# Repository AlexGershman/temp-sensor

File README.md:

# temp-sensor
This repo is dedicated to storing the schematic, layout, and symbol files of the temperature sensor circuit board for ECE 115D.

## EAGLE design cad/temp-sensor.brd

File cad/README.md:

In the CAD folder, we store files such as the BOM, schematic, board, and any new symbols.

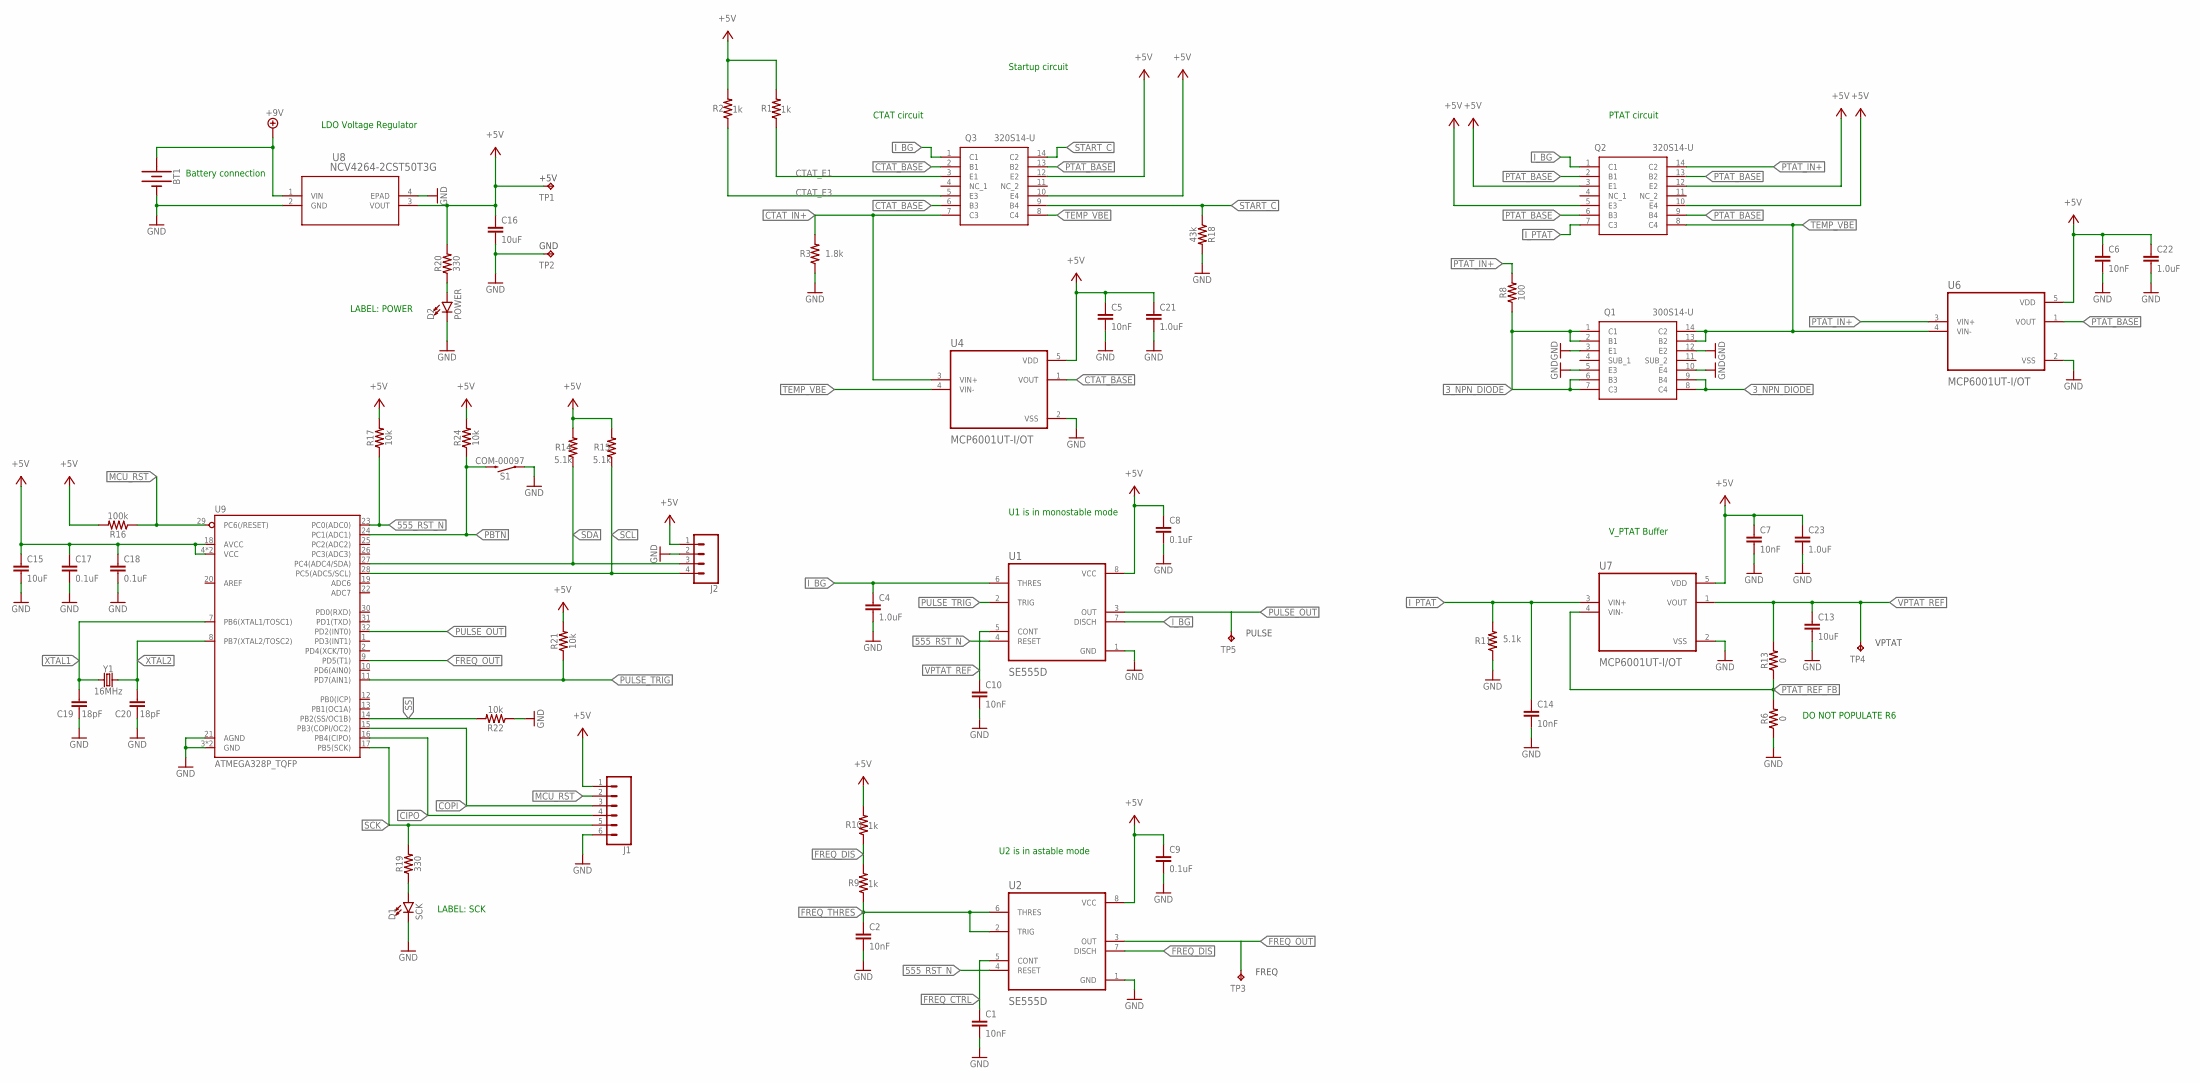
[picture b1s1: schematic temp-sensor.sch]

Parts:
BT1: BATTERY-9V; BATTCON_9V
C1, C2, C5, C6, C7, C10, C14: 10nF; 0603
C4, C21, C22, C23: 1.0uF; 0603
C8, C9, C17, C18: 0.1uF; 0603
C13, C15, C16: 10uF; 0805
C19, C20: 18pF; 0603
D1: SCK; LED-1206
D2: POWER; LED-1206
J1: CONN_06SILK_FEMALE_PTH; 1X06
J2: CONN_04PTH; 1X04
Q1: 300S14-U; SOIC127P602X175-14N
Q2, Q3: 320S14-U; SOIC127P602X175-14N
R1, R2, R9, R10: 1k; 0603
R3: 1.8k; 0603
R6, R13: 0; 0603
R8: 100; 0603
R11, R14, R15: 5.1k; 0603
R16: 100k; 0603
R17, R21, R22, R24: 10k; 0603
R18: 43k; 0603
R19, R20: 330; 0603
S1: MOMENTARY-SWITCH-SPST-PTH-6.0MM; TACTILE_SWITCH_PTH_6.0MM
TP1, TP2, TP3, TP4, TP5: TPPAD1-13; P1-13
U1, U2: SE555D; SOIC127P599X175-8N
U4, U6, U7: MCP6001UT-I/OT; SOT95P270X145-5N
U8: NCV4264-2CST50T3G; SOT-223_ONS
U9: ATMEGA328P_TQFP; TQFP32-08
Y1: 16MHz; CRYSTAL-SMD-5X3.2-4PAD

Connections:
3_NPN_DIODE: Q1.1 (C1), Q1.2 (B1), Q1.6 (B3), Q1.7 (C3), Q1.8 (C4), Q1.9 (B4), R8.1
555_RST_N: R17.1, U1.4 (RESET), U2.4 (RESET), U9.23 (PC0(ADC0))
+5V: C5.1, C6.1, C7.1, C8.1, C9.1, C15.1, C16.1, C17.1, C18.1, C21.1, C22.1, C23.1, J1.1, J2.1, Q2.3 (E1), Q2.5 (E3), Q2.10 (E4), Q2.12 (E2), Q3.10 (E4), Q3.12 (E2), R1.2, R2.2, R10.2, R14.2, R15.2, R16.2, R17.2, R20.2, R21.2, R24.2, TP1.TP, U1.8 (VCC), U2.8 (VCC), U4.5 (VDD), U6.5 (VDD), U7.5 (VDD), U8.3 (VOUT), U9.4 (VCC), U9.6 (VCC), U9.18 (AVCC)
+9V: BT1.+, U8.1 (VIN)
CIPO: J1.4, U9.16 (PB4(CIPO))
COPI: J1.3, U9.15 (PB3(COPI/OC2))
CTAT_BASE: Q3.2 (B1), Q3.6 (B3), U4.1 (VOUT)
CTAT_E1: Q3.3 (E1), R1.1
CTAT_E3: Q3.5 (E3), R2.1
CTAT_IN+: Q3.7 (C3), R3.2, U4.3 (VIN+)
FREQ_CTRL: C1.1, U2.5 (CONT)
FREQ_DIS: R9.2, R10.1, U2.7 (DISCH)
FREQ_OUT: TP3.TP, U2.3 (OUT), U9.9 (PD5(T1))
FREQ_THRES: C2.1, R9.1, U2.2 (TRIG), U2.6 (THRES)
GND: BT1.-, C1.2, C2.2, C4.2, C5.2, C6.2, C7.2, C8.2, C9.2, C10.2, C13.2, C14.2, C15.2, C16.2, C17.2, C18.2, C19.1, C20.1, C21.2, C22.2, C23.2, D1.C, D2.C, J1.6, J2.2, Q1.3 (E1), Q1.5 (E3), Q1.10 (E4), Q1.12 (E2), R3.1, R6.1, R11.1, R18.2, R22.1, S1.1, TP2.TP, U1.1 (GND), U2.1 (GND), U4.2 (VSS), U6.2 (VSS), U7.2 (VSS), U8.2 (GND), U8.4 (EPAD), U9.3 (GND), U9.5 (GND), U9.21 (AGND)
I_BG: C4.1, Q2.1 (C1), Q3.1 (C1), U1.6 (THRES), U1.7 (DISCH)
I_PTAT: C14.1, Q2.7 (C3), R11.2, U7.3 (VIN+)
MCU_RST: J1.2, R16.1, U9.29 (PC6(/RESET))
unnamed: D1.A, R19.1
unnamed: D2.A, R20.1
PBTN: R24.1, S1.3 (2), U9.24 (PC1(ADC1))
PTAT_BASE: Q2.2 (B1), Q2.6 (B3), Q2.9 (B4), Q2.13 (B2), Q3.13 (B2), U6.1 (VOUT)
PTAT_IN+: Q2.14 (C2), R8.2, U6.3 (VIN+)
PTAT_REF_FB: R6.2, R13.1, U7.4 (VIN-)
PULSE_OUT: TP5.TP, U1.3 (OUT), U9.32 (PD2(INT0))
PULSE_TRIG: R21.1, U1.2 (TRIG), U9.11 (PD7(AIN1))
SCK: J1.5, R19.2, U9.17 (PB5(SCK))
SCL: J2.4, R15.1, U9.28 (PC5(ADC5/SCL))
SDA: J2.3, R14.1, U9.27 (PC4(ADC4/SDA))
SS: R22.2, U9.14 (PB2(SS/OC1B))
START_C: Q3.9 (B4), Q3.14 (C2), R18.1
TEMP_VBE: Q1.13 (B2), Q1.14 (C2), Q2.8 (C4), Q3.8 (C4), U4.4 (VIN-), U6.4 (VIN-)
VPTAT_REF: C10.1, C13.1, R13.2, TP4.TP, U1.5 (CONT), U7.1 (VOUT)
XTAL1: C19.2, U9.7 (PB6(XTAL1/TOSC1)), Y1.1
XTAL2: C20.2, U9.8 (PB7(XTAL2/TOSC2)), Y1.3 (2)

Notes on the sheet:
U1 is in monostable mode
Startup circuit
CTAT circuit
PTAT circuit
V_PTAT Buffer
U2 is in astable mode
DO NOT POPULATE R6
LDO Voltage Regulator
Battery connection
LABEL: POWER
LABEL: SCK

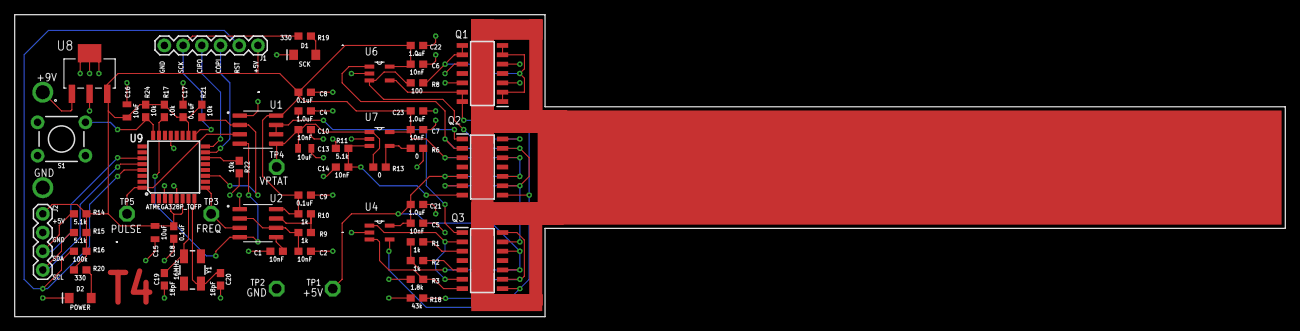
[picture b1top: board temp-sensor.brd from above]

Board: 2 copper layers, 172.5 x 41.0 mm, 61 parts (1 on the bottom side), 35 nets.

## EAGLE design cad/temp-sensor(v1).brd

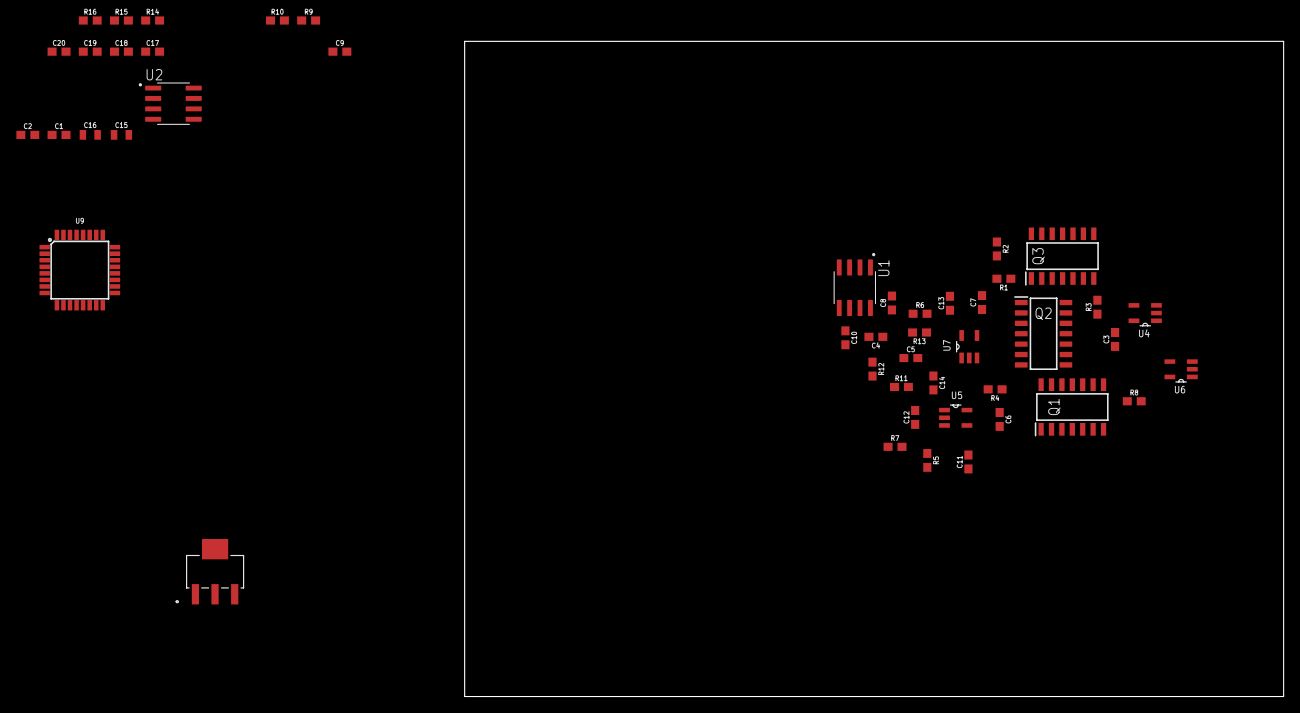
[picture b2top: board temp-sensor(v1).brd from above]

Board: 2 copper layers, 100.0 x 80.0 mm, 47 parts (0 on the bottom side), 25 nets, no tracks yet.

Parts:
C1, C2, C10, C11, C12, C13, C14: 10nF; 0603
C3, C5, C6, C7, C8, C9, C17, C18: 0.1uF; 0603
C4: 1.0uF; 0603
C15, C16: 10uF; 0805
C19, C20: 18pF; 0603
Q1: 300S14-U; SOIC127P602X175-14N
Q2, Q3: 320S14-U; SOIC127P602X175-14N
R1, R2, R9, R10: 1k; 0603
R3: 1.8k; 0603
R4, R16: 100k; 0603
R5: 200k; 0603
R6, R13: 0; 0603
R7, R11, R14, R15: 5.1k; 0603
R8: 100; 0603
R12: 10k; 0603
U1, U2: SE555D; SOIC127P599X175-8N
U4, U5, U6, U7: MCP6001UT-I/OT; SOT95P270X145-5N
U8: NCV4264-2CST50T3G; SOT-223_ONS
U9: ATMEGA328P_TQFP; TQFP32-08

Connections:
3_NPN_DIODE: Q1.1, Q1.2, Q1.6, Q1.7, Q1.8, Q1.9, R8.1
+5V: C3.1, C5.1, C6.1, C7.1, C8.1, C9.1, C15.1, C16.1, C17.1, C18.1, Q2.3, Q2.5, Q2.10, Q2.12, R1.2, R2.2, R14.2, R15.2, R16.2, U1.8, U2.8, U4.5, U5.5, U6.5, U7.5, U8.3, U9.4, U9.6, U9.18
BG_REF_FB: C11.1, R4.1, R5.2, U5.4
CTAT_BASE: Q3.2, Q3.6, U4.1
CTAT_E1: Q3.3, R2.1
CTAT_E3: Q3.5, R1.1
CTAT_IN+: Q3.7, R3.2, U4.3
FREQ_DIS: R9.2, R10.1, U2.7
FREQ_THRES: C2.1, R9.1, U2.2, U2.6
GND: C1.2, C2.2, C3.2, C4.2, C5.2, C6.2, C7.2, C8.2, C9.2, C10.2, C11.2, C12.2, C13.2, C14.2, C15.2, C16.2, C17.2, C18.2, C19.1, C20.1, Q1.3, Q1.5, Q1.10, Q1.12, R3.1, R5.1, R6.1, R7.1, R11.1, U1.1, U2.1, U4.2, U5.2, U6.2, U7.2, U8.2, U8.4, U9.3, U9.5, U9.21
I_BG: C12.1, Q2.1, Q3.1, R7.2, U5.3
I_PTAT: C14.1, Q2.7, R11.2, U7.3
MCU_RST: R16.1, U9.29
unnamed: C19.2, U9.7
unnamed: C20.2, U9.8
unnamed: C1.1, U2.5
PTAT_BASE: Q2.2, Q2.6, Q2.9, Q2.13, U6.1
PTAT_IN+: Q2.14, R8.2, U6.3
PTAT_REF_FB: C13.1, R6.2, R13.1, U7.4
PULSE_THRES: C4.1, R12.1, U1.6
SCL: R15.1, U9.28
SDA: R14.1, U9.27
TEMP_VBE: Q1.13, Q1.14, Q2.8, Q3.8, U4.4, U6.4
VBG_REF: R4.2, R10.2, R12.2, U5.1
VPTAT_REF: C10.1, R13.2, U1.5, U7.1

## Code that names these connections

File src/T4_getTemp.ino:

#include <Arduino.h>
#include <avr/io.h>
#include <avr/interrupt.h>
#include <avr/sleep.h>
#include <Adafruit_GFX.h>
#include <Adafruit_SSD1306.h>
#include <stdio.h> 

#define PULSE_INPUT_PIN PD5  // T1 pin (freq out astable output)
#define STOP_COUNT_PIN PD2   // INT0 pin (pulse out, stop on this falling edge)
#define TRIGGER_PIN PC0      // Trigger pin for 555 rst n
#define PULSE_TRIGGER_PIN PD7 // Pulse trigger pin

#define SCREEN_WIDTH 128 // OLED display width, in pixels
#define SCREEN_HEIGHT 32 // OLED display height, in pixels
#define OLED_RESET -1 // Reset pin # (or -1 if sharing Arduino reset pin)

#define CHAR_DISPLAYED 3 // Number of characters to display on OLED

Adafruit_SSD1306 display(SCREEN_WIDTH, SCREEN_HEIGHT, &Wire, OLED_RESET); // Declaring the OLED name

const float pulsesToTempFactor = 0.3363;
const float pulsesToTempOffset = -273;

volatile uint32_t pulseCount = 0; // use uint16_t depending on how many pulses
volatile bool countingEnabled = true;
volatile bool stopCounting = false;

volatile uint32_t pulseCountInInterval = 0; // Pulse count within the interval
uint32_t totalPulseCount = 0; // Total pulse count over multiple triggers
uint8_t triggerCount = 0; // Number of triggers

const float numTriggersForAverage = 5; // Number of triggers to average over

void setup() {
  // Initialize serial communication for debugging
  Serial.begin(9600);
  display.begin(SSD1306_SWITCHCAPVCC, 0x3C); // Start the OLED display
  display.display();
  delay(3000);

  // Configure the pushbutton
  PCMSK1 |= (1 << PCINT9);  // Enable PC1
  PCICR |= (1 << PCIE1);    // Set PC1 as an interrupt

  // Configure Timer1 for desired settings
  TCCR1B |= (1 << CS11) | (1 << CS10) | (1<< CS12); //Enable external clock input
  OCR1A = 0xFFFF; // Set output compare register to maximum value for max period

  // Configure the stop count pin as input
  DDRD &= ~(1 << STOP_COUNT_PIN);  // Set PD2 as input
  PORTD |= (0 << STOP_COUNT_PIN);  // Enable pull-down resistor on PD2

  // Configure the trigger pin as output
  DDRC |= (1 << TRIGGER_PIN);    // Set PC0 as output

  // Configure the pulse trigger pin as output
  DDRD |= (1 << PULSE_TRIGGER_PIN); // Set PD7 as output

  // Ensure pulse trigger pin is initially high
  PORTD |= (1 << PULSE_TRIGGER_PIN); // Set PD7 high

  // Configure Timer/Counter1 for counting rising edges on T1 (PD5)
  TCCR1A = 0; // Normal mode
  TCCR1B |= (1 << ICES1); // Input capture on rising edge
  TIMSK1 |= (1 << ICIE1); // Enable input capture interrupt

  // Configure external interrupt INT0 for falling edge trigger
  EICRA |= (1 << ISC01);  // Trigger on falling edge (ISC01 = 1, ISC00 = 0)
  EIMSK |= (1 << INT0);   // Enable INT0 interrupt

  // Sleep until interupted by button
  set_sleep_mode(SLEEP_MODE_PWR_DOWN);
  sei(); // Enable global interrupts
}

void loop() {
  if (!countingEnabled) {
    display.clearDisplay();
    display.setTextSize(2);
    display.setTextColor(WHITE);
    display.setCursor(0, 0);
    display.println("Sleeping");
    display.display();
    delay(2000);
    display.ssd1306_command(0xAE); //Disable display
    cli();
    sleep_enable();
    sei(); // Enable global interrupts
    sleep_cpu();
    sleep_disable();
    return;
  }

  PORTC |= (1 << TRIGGER_PIN); // Enable the 555 timers
  delay(100); // Wait for 50ms
  PORTD &= ~(1 << PULSE_TRIGGER_PIN); // Set PD7 low (pulse trigger), trigger the pulse
  TCNT1 = 0;  // Reset microcontroller counter
  PORTD |= (1 << PULSE_TRIGGER_PIN);  // Set PD7 high again to finish the pulse, untrigger the pulse

  if (triggerCount >= numTriggersForAverage) {
    float averagePulseCount = totalPulseCount / numTriggersForAverage;
    float temperatureC = convertPulsesToTemp(averagePulseCount);
    float temperatureF = (temperatureC * 9.0/5.0) + 32.0;
    //char temp_str[CHAR_DISPLAYED]; 
    //snprintf(temp_str, CHAR_DISPLAYED, "%.2", temperature); // Convert temp float to string stored in temp_str

    display.clearDisplay();
    display.setTextSize(2);
    display.setTextColor(WHITE);
    display.setCursor(0, 0);
    display.print(temperatureC);
    display.println(" degC");
    display.setCursor(0, 16);
    display.print(temperatureF);
    display.println(" degF");
    display.display();
    // Display for 10 seconds
    delay(10000);

    // Reset counters for next averaging period
    totalPulseCount = 0;
    triggerCount = 0;

    // Enable sleep mode
    //SMCR |= (1 << SE);
    // Sleep until interupted by button
    //sleep_cpu();
  }
}

// Interrupt Service Routine (ISR) for INT0 external interrupt
ISR(INT0_vect) {
  pulseCount = TCNT1; // Read pulse count register
  countingEnabled = false; // Stop counting
  totalPulseCount += pulseCount; //Add all the current pulses to the total counter for averaging
  triggerCount++; //To keep track of the number of triggers
  pulseCount = 0; //Reset pulse count to 0 for the next iteration

  if (triggerCount < numTriggersForAverage) {
    countingEnabled = true;
  }
}

// Interrupt Service Routine (ISR) for PCINT9 external interrupt
ISR(PCINT0_vect) {
  //SMCR &= (0 << SE);
  triggerCount = 0;
  countingEnabled = true; 
}

float convertPulsesToTemp(unsigned int pulses) {
  return (pulses * pulsesToTempFactor) + pulsesToTempOffset;
}

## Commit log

2024-04-02 Add initial LTSpice schematic
    Simulation schematic includes the Bandgap and PTAT references voltages, one 555 timer in the mono-stable mode (U1), and one 555 timer in the a-stable mode (U2). This outlines the basic architecture o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
2024-04-05 Add files via upload
    test
2024-04-05 stuff
    add resistor
2024-04-06 Test
    Test1 delete resistor
2024-04-08 initialize libraries
2024-04-08 initialized schematic
    LTSpice implementation
2024-04-08 Add files via upload
    Combined startup circuit IC and bandgap IC
2024-04-08 Add files via upload
    combined startup circuit IC into bandgap IC
2024-04-08 Spencer's schematic additions
2024-04-09 LTspice with LDO
    initial LDO design
2024-04-14 Adding real op-amps
    Add real op-amps to PTAT/BG circuit and their references. Needed to add a little gain to BG reference op-amp to ensure it can charge the astable timer capacitor above the 2/3 VCC (of 5V = 3.33V).
2024-04-18 Fix file location
2024-04-18 Delete cad/ECE_115D_555_Timer_IC.asc
    Remove file from wrong location
2024-04-20 Add MCU and LDO, Initialize .BRD file
2024-04-21 Add files via upload
    Both board files are preliminary layouts. Not all components are present. temp-sensor(v1) was my first pass of beginning the layout.
2024-04-21 Connect MCU
    Add MCU connection to 555 timers, add correct bypass caps for opamps, add battery holder, add LEDs for PWR_ON/SCK signals, add 6-pin header for SPI programming + MCU reset
2024-04-22 Added start up circuit
2024-04-22 Add files via upload
    preliminary design for enclosure for pcb, screen, plate, and 9V battery
2024-04-22 Initialize part placement
2024-04-22 Initialize layout file
2024-04-22 Add placement and passives
2024-04-23 Finished Layout and schematic
    (took out C11 and C13)
    Layout can be cleaned up?
2024-04-23 Finalized Schematic and Layout
    Got rid of C11 and C13 since they were causing oscillations
2024-04-23 Finalized Layout
    condensed board
2024-04-27 Edit placement
2024-04-27 Edit placement again
2024-04-28 Initial routing
    Still need to add test points and clean up silk screen.
2024-04-28 Clean up silk and add test points
2024-04-28 Add 4 pin header for OLED
2024-04-29 Finishing touches on silk
2024-04-29 Removed +5V power plane
    Removed +5V power plane. Instead, +5V was routed with 12 mil traces
2024-04-30 Presentation comments
    Removed V_BG buffer. Now feeding I_BG current source to input capacitor of monostable timer. Rerouted with 6 mil traces.
2024-04-30 Changes from midterm presentation
    Changes from midterm presentation including feeding mono stable timer with bandgap current source and a capacitor. This produces a linear voltage since Ic = C dV/dt.
2024-05-01 Modified sim for linear temp relation
2024-05-02 changed temp simulation
2024-05-06 Layout change for exposed copper pad
    Removed the vias and routing under Q1, Q2, Q3 matched transistors to make space for a thermally conductive exposed copper pad
2024-05-07 Add files via upload
    Implemented plate extension for temperature reading
2024-05-08 Adjust grid and via placement
2024-05-08 Boards ordered!
2024-05-28 init working code
    This implementation has the following characteristics
    1) Triggers the monostable timer
    2) Counts clock from astable timer
    3) Stops counting on falling edge of monostable timer
    4) Pushbutton triggers a new measurement
2024-05-28 Correcting file location
2024-06-01 Add sleep capability for power saving

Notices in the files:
parts and their libraries:
SparkFun-Capacitors: Licensing: Creative Commons ShareAlike 4.0 International - https://creativecommons.org/licenses/by-sa/4.0
COPYRIGHT: Copyright (C) 2024 Ultra Librarian. All rights reserved.
